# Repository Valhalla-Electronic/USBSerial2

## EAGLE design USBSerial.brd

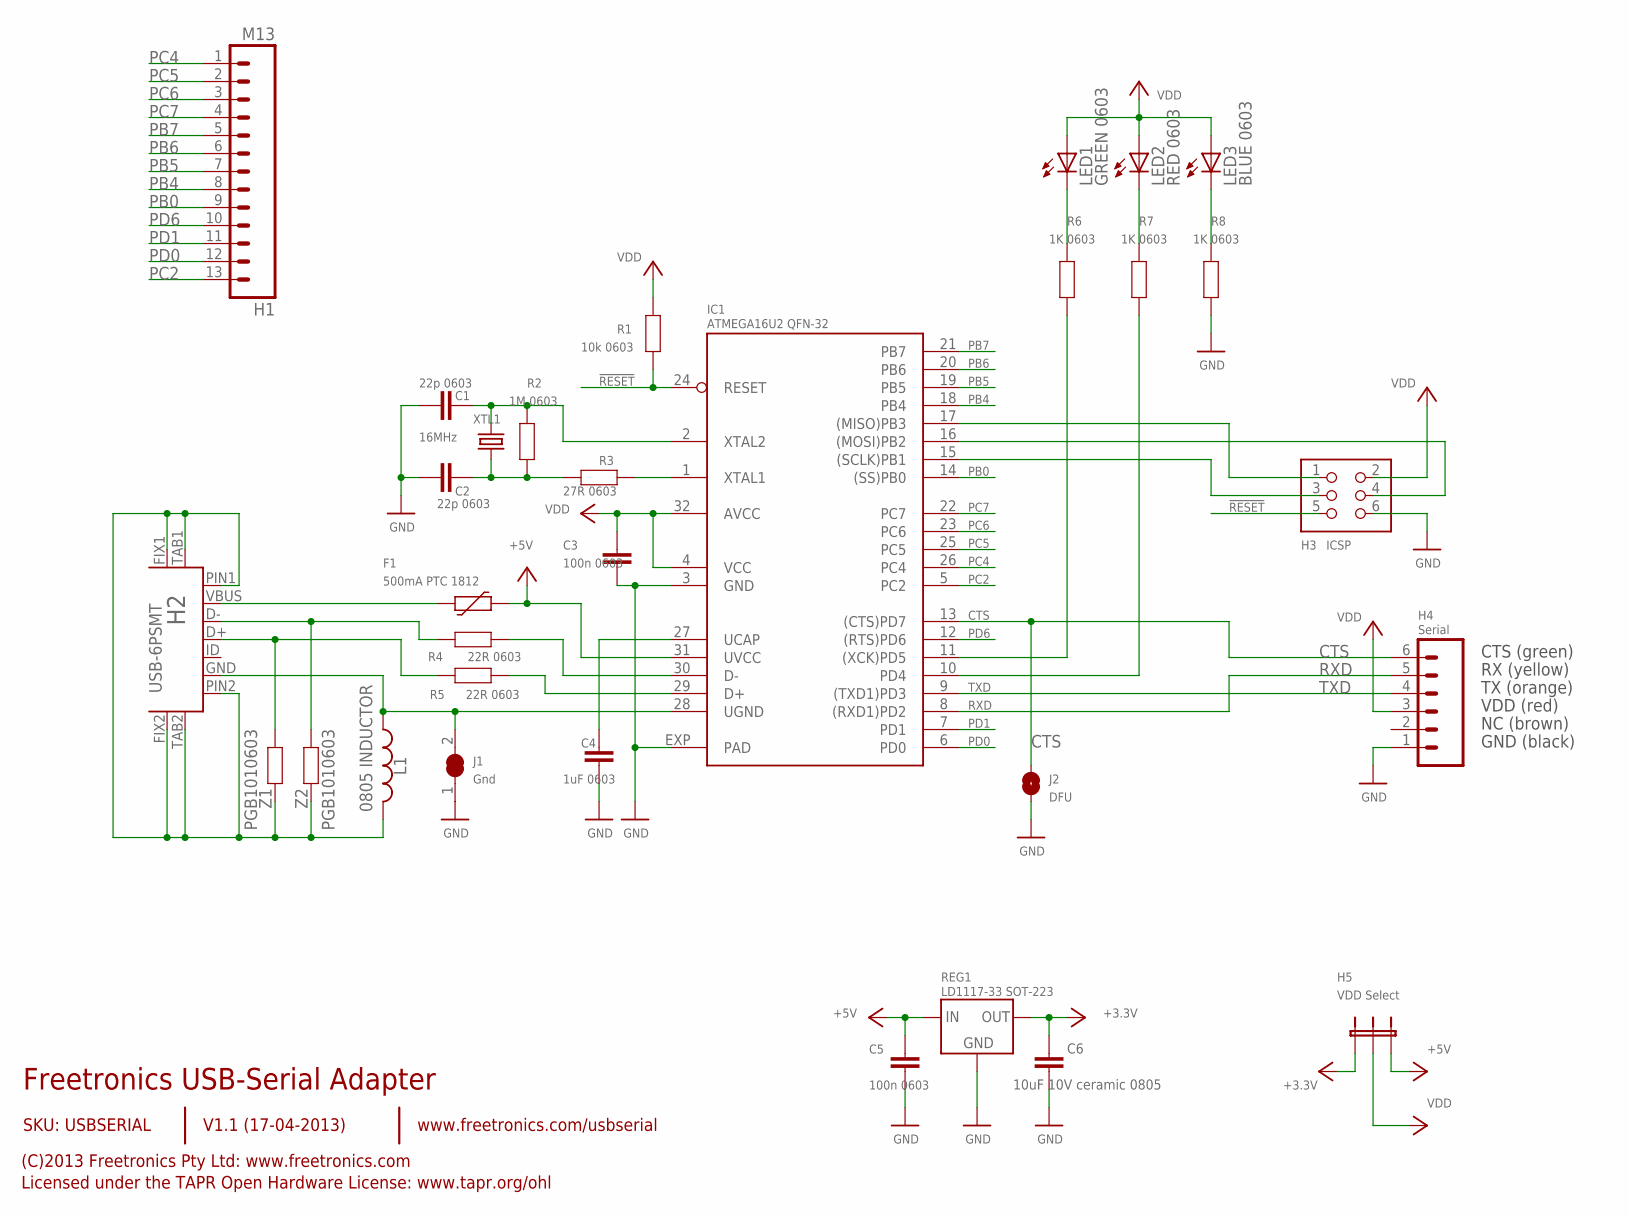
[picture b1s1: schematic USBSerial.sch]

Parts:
C1, C2: 22p 0603; 0603
C3, C5: 100n 0603; 0603
C4: 1uF 0603; 0603
C6: 10uF 10V ceramic 0805; C0805
F1: 500mA PTC 1812; 1812
H1: M13; 1X13
H2: USB-6PSMT; USB-MICROB-MB05PMXX
H3: ICSP; HEADER_2X3
H4: Serial; 1X06
H5: VDD Select; JUMPER_SPDT
IC1: ATMEGA16U2 QFN-32; ATMEL_QFN32
J1: Gnd; SJC
J2: DFU; SJ
L1: 0805 INDUCTOR; 0805-LARGE
LED1: GREEN 0603; LED-0603
LED2: RED 0603; LED-0603
LED3: BLUE 0603; LED-0603
R1: 10k 0603; 0603
R2: 1M 0603; 0603
R3: 27R 0603; 0603
R4, R5: 22R 0603; 0603
R6, R7, R8: 1K 0603; 0603
REG1: LD1117-33 SOT-223; SOT-223
XTL1: 16MHz; HC49US
Z1, Z2: PGB1010603; 0603

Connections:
!RESET: H3.5, IC1.24 (RESET), R1.1
+3V3: C6.1, H5.1, REG1.2 (OUT), REG1.4 (OUT)
+5V: C5.1, F1.2, H5.3, IC1.31 (UVCC), REG1.3 (IN)
CTS: H4.6, IC1.13 ((CTS)PD7), J2.2
GND: C1.1, C2.1, C3.2, C4.2, C5.2, C6.2, H3.6, H4.1, IC1.3 (GND), IC1.EXP (PAD), J1.1, J2.1, R8.1, REG1.1 (GND)
MISO: H3.1, IC1.17 ((MISO)PB3)
MOSI: H3.4, IC1.16 ((MOSI)PB2)
unnamed: H2.GND, IC1.28 (UGND), J1.2, L1.1
unnamed: IC1.1 (XTAL1), R3.1
unnamed: LED1.C, R6.2
unnamed: LED2.C, R7.2
unnamed: H2.FIX1, H2.FIX2, H2.PIN1, H2.PIN2, H2.TAB1, H2.TAB2, L1.2, Z1.2, Z2.2
unnamed: LED3.C, R8.2
unnamed: H2.D+, R5.2, Z1.1
unnamed: H2.D-, R4.2, Z2.1
unnamed: C1.2, IC1.2 (XTAL2), R2.2, XTL1.2
unnamed: C2.2, R2.1, R3.2, XTL1.1
unnamed: F1.1, H2.VBUS
unnamed: C4.1, IC1.27 (UCAP)
PB0: H1.9, IC1.14 ((SS)PB0)
PB4: H1.8, IC1.18 (PB4)
PB5: H1.7, IC1.19 (PB5)
PB6: H1.6, IC1.20 (PB6)
PB7: H1.5, IC1.21 (PB7)
PC2: H1.13, IC1.5 (PC2)
PC4: H1.1, IC1.26 (PC4)
PC5: H1.2, IC1.25 (PC5)
PC6: H1.3, IC1.23 (PC6)
PC7: H1.4, IC1.22 (PC7)
PD0: H1.12, IC1.6 (PD0)
PD1: H1.11, IC1.7 (PD1)
PD6: H1.10, IC1.12 ((RTS)PD6)
RD+: IC1.29 (D+), R5.1
RD-: IC1.30 (D-), R4.1
RXD: H4.5, IC1.8 ((RXD1)PD2)
RXLED: IC1.10 (PD4), R7.1
SCK: H3.3, IC1.15 ((SCLK)PB1)
TXD: H4.4, IC1.9 ((TXD1)PD3)
TXLED: IC1.11 ((XCK)PD5), R6.1
VDD: C3.1, H3.2, H4.3, H5.2, IC1.4 (VCC), IC1.32 (AVCC), LED1.A, LED2.A, LED3.A, R1.2

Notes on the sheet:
Freetronics USB-Serial Adapter
V1.1 (17-04-2013)
SKU: USBSERIAL
(C)2013 Freetronics Pty Ltd: www.freetronics.com
Licensed under the TAPR Open Hardware License: www.tapr.org/ohl
www.freetronics.com/usbserial
CTS (green)
RX (yellow)
TX (orange)
VDD (red)
NC (brown)
GND (black)

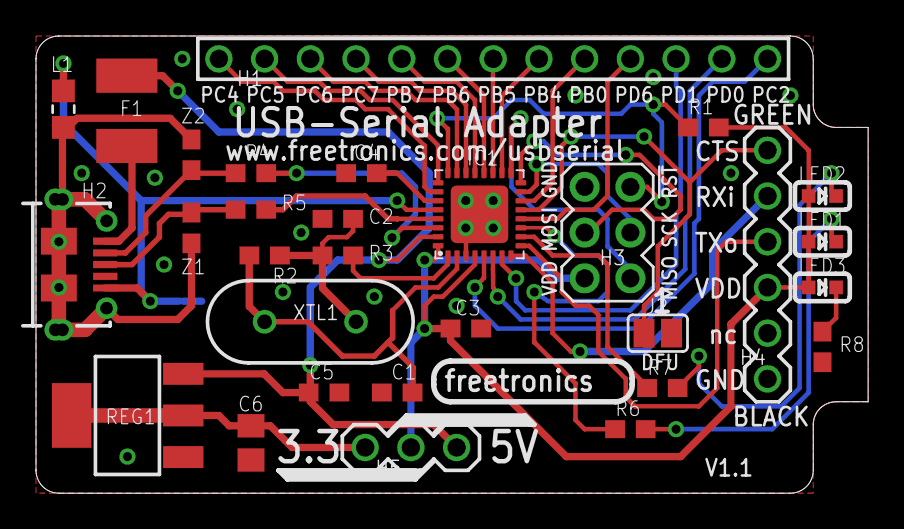
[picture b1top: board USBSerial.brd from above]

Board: 2 copper layers, 46.2 x 25.4 mm, 31 parts (1 on the bottom side), 40 nets.

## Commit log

2013-04-17 Changed CTS / RTS assignment
2013-04-17 v1.1 release: Separate LEDs near TX/RX/VCC pins; PCB tab over connector; label improvements
2014-01-17 Add README, schematic PDF
2018-11-04 Minor cleanups for v1.2 release
2019-04-24 Replaced USB connector with USB-C
2019-04-24 Renamed project files
